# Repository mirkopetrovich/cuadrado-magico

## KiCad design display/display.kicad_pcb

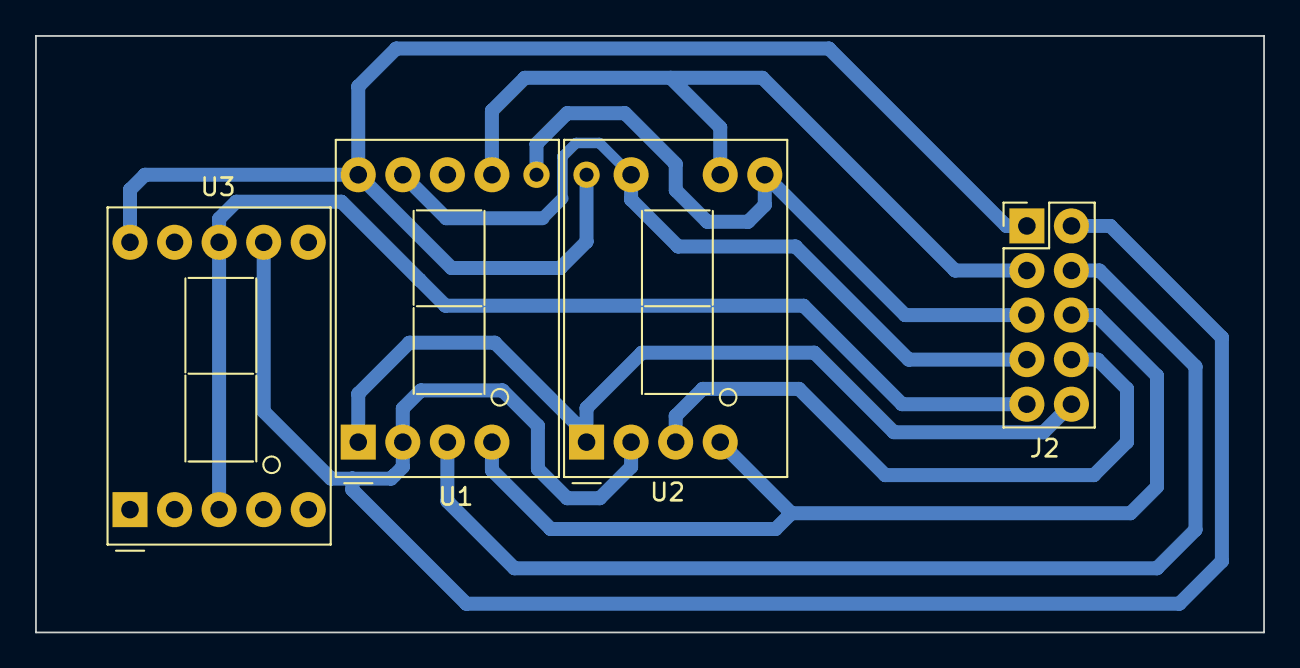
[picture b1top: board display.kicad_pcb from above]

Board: 2 copper layers, 70.0 x 34.0 mm, 4 parts (0 on the bottom side), 10 nets.

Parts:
J2: Conn_02x05_Odd_Even; PinHeader_2x05_P2.54mm_Vertical
U1, U2, U3: D148K; D1X8K

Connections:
/a: J2.3, U1.7 (A), U2.7 (A)
/b: J2.5, U1.6 (B), U2.6 (B)
/c: J2.6, U1.4 (C), U2.4 (C)
/cs1: J2.4, U1.3 (CC), U1.8 (CC)
/cs2: J2.8, U2.3 (CC)
/cs3: J2.9, U3.3 (CC), U3.8 (CC)
/d: J2.2, U1.2 (D), U2.2 (D), U3.7 (A)
/e: J2.10, U1.1 (E), U2.1 (E)
/f: J2.7, U1.9 (F), U2.9 (F)
/g: J2.1, U1.10 (G), U2.10 (G), U3.10 (G)

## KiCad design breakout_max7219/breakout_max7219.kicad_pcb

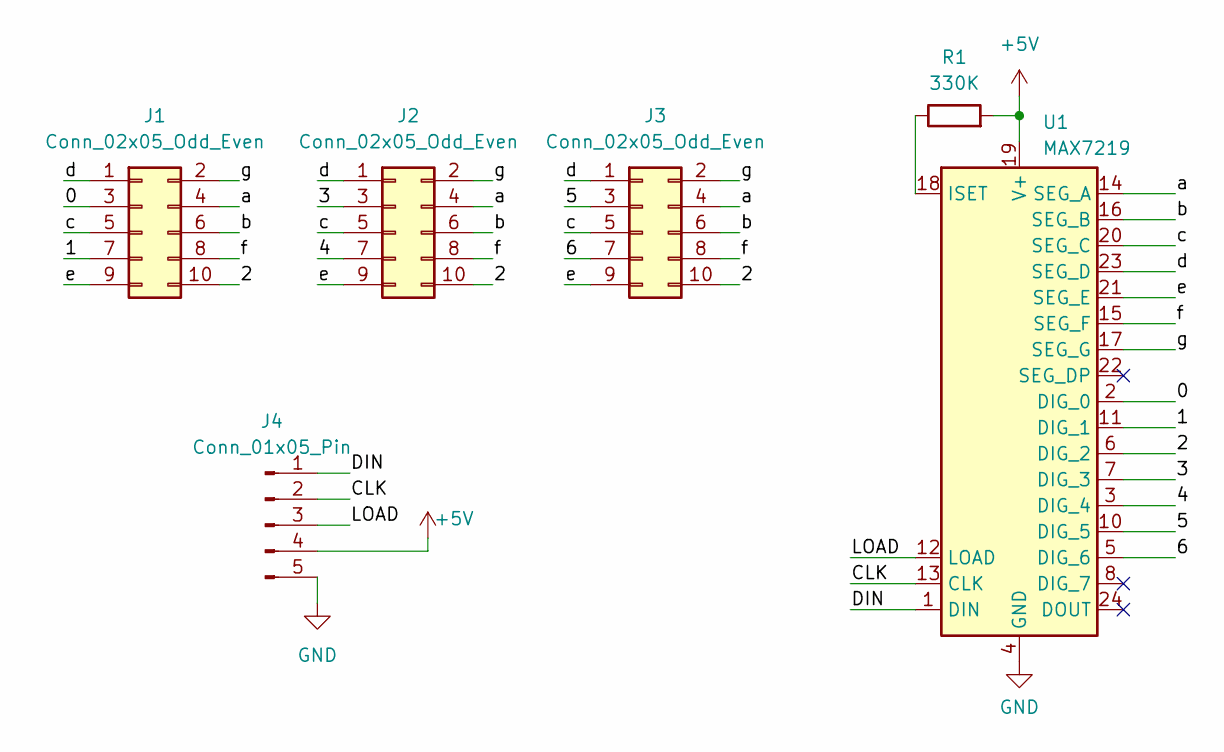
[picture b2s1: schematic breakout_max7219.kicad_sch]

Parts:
J1, J2, J3: Conn_02x05_Odd_Even; PinHeader_2x05_P2.54mm_Vertical
J4: Conn_01x05_Pin; PinHeader_1x05_P2.54mm_Vertical
R1: 330K; R_Axial_DIN0207_L6.3mm_D2.5mm_P10.16mm_Horizontal
U1: MAX7219; DIP-24_W7.62mm_Socket

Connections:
+5V: J4.4, R1.2, U1.19 (V+)
/0: J1.3, U1.2 (DIG_0)
/1: J1.7, U1.11 (DIG_1)
/2: J1.10, J2.10, J3.10, U1.6 (DIG_2)
/3: J2.3, U1.7 (DIG_3)
/4: J2.7, U1.3 (DIG_4)
/5: J3.3, U1.10 (DIG_5)
/6: J3.7, U1.5 (DIG_6)
/CLK: J4.2, U1.13 (CLK)
/DIN: J4.1, U1.1 (DIN)
/LOAD: J4.3, U1.12 (LOAD)
/a: J1.4, J2.4, J3.4, U1.14 (SEG_A)
/b: J1.6, J2.6, J3.6, U1.16 (SEG_B)
/c: J1.5, J2.5, J3.5, U1.20 (SEG_C)
/d: J1.1, J2.1, J3.1, U1.23 (SEG_D)
/e: J1.9, J2.9, J3.9, U1.21 (SEG_E)
/f: J1.8, J2.8, J3.8, U1.15 (SEG_F)
/g: J1.2, J2.2, J3.2, U1.17 (SEG_G)
GND: J4.5, U1.4 (GND), U1.9 (GND)
unnamed: R1.1, U1.18 (ISET)

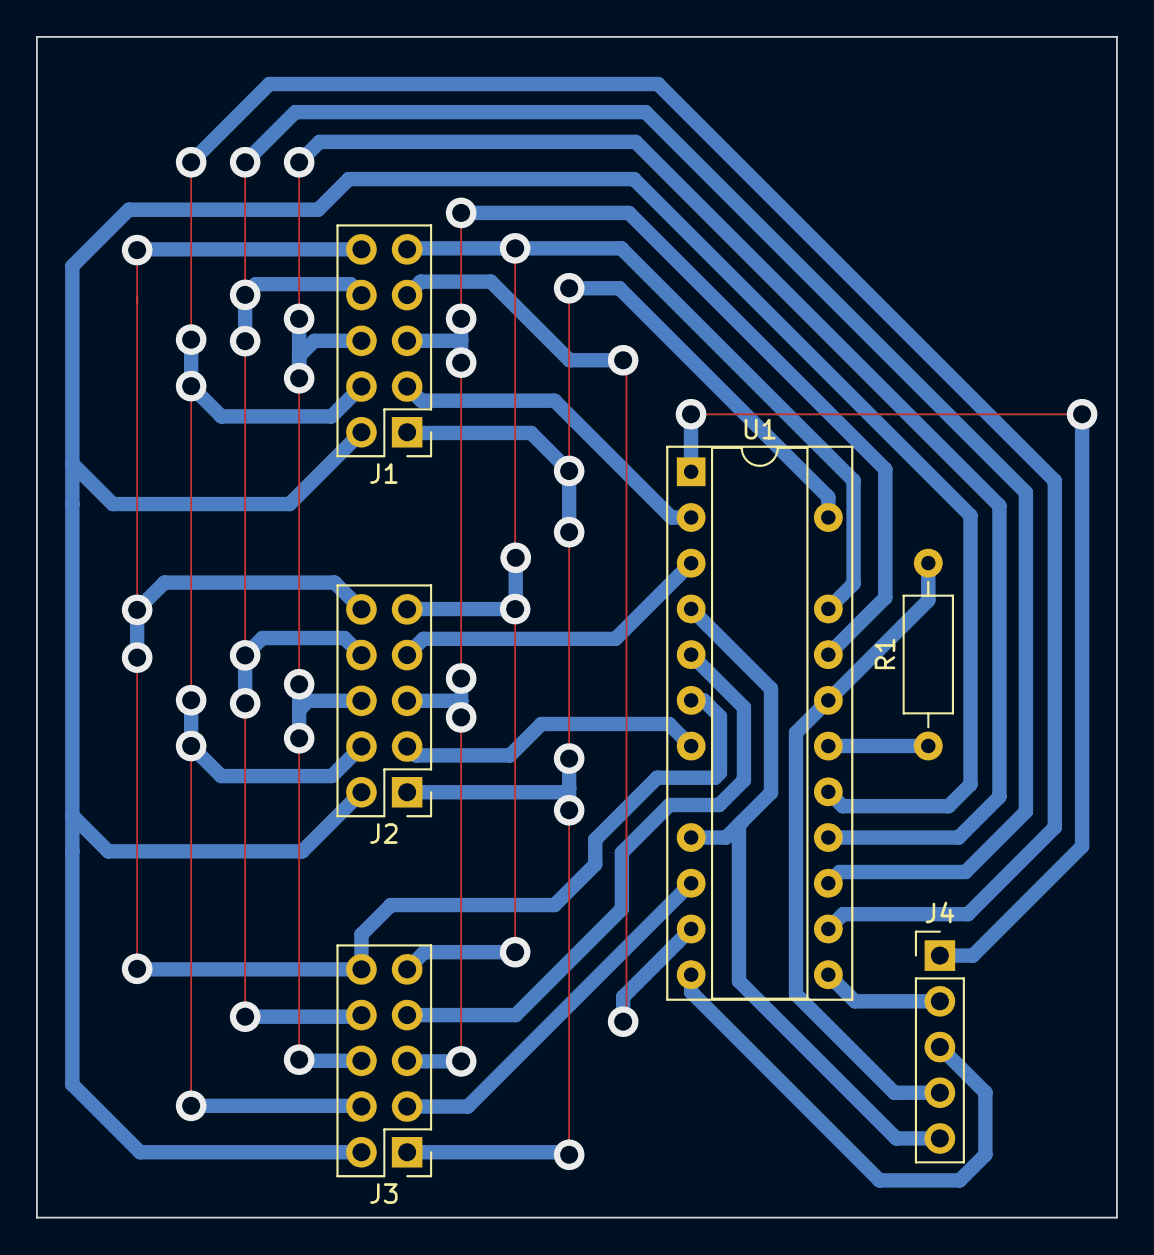
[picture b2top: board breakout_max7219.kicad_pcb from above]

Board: 2 copper layers, 60.0 x 65.6 mm, 6 parts (0 on the bottom side), 20 nets.

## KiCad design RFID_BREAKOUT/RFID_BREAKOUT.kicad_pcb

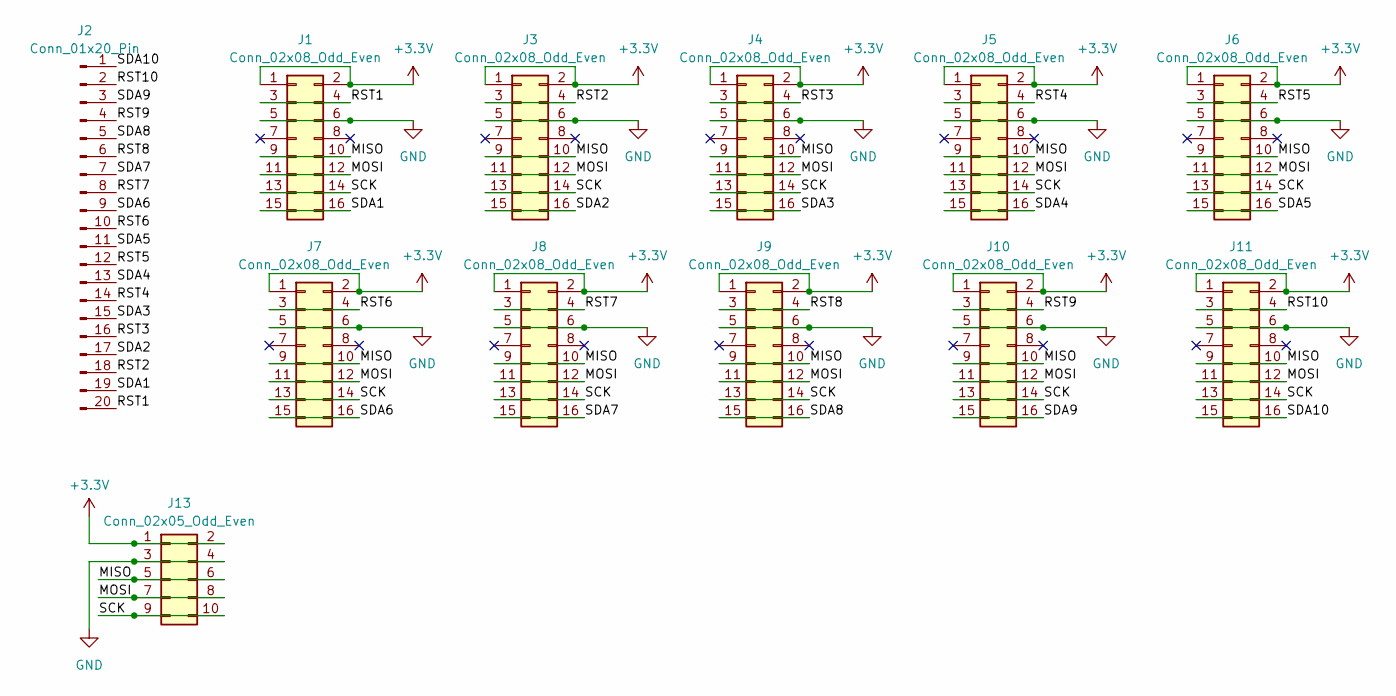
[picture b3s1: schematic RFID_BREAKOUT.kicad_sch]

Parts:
J1, J3, J4, J5, J6, J7, J8, J9, J10, J11: Conn_02x08_Odd_Even; PinHeader_2x08_P2.54mm_Vertical
J2: Conn_01x20_Pin; PinHeader_2x10_P2.54mm_Vertical
J13: Conn_02x05_Odd_Even; PinHeader_2x05_P2.54mm_Vertical

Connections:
+3.3V: J1.1, J1.2, J3.1, J3.2, J4.1, J4.2, J5.1, J5.2, J6.1, J6.2, J7.1, J7.2, J8.1, J8.2, J9.1, J9.2, J10.1, J10.2, J11.1, J11.2, J13.1, J13.2
/MISO: J1.9, J1.10, J3.9, J3.10, J4.9, J4.10, J5.9, J5.10, J6.9, J6.10, J7.9, J7.10, J8.9, J8.10, J9.9, J9.10, J10.9, J10.10, J11.9, J11.10, J13.5, J13.6
/MOSI: J1.11, J1.12, J3.11, J3.12, J4.11, J4.12, J5.11, J5.12, J6.11, J6.12, J7.11, J7.12, J8.11, J8.12, J9.11, J9.12, J10.11, J10.12, J11.11, J11.12, J13.7, J13.8
/RST1: J1.3, J1.4, J2.20
/RST2: J2.18, J3.3, J3.4
/RST3: J2.16, J4.3, J4.4
/RST4: J2.14, J5.3, J5.4
/RST5: J2.12, J6.3, J6.4
/RST6: J2.10, J7.3, J7.4
/RST7: J2.8, J8.3, J8.4
/RST8: J2.6, J9.3, J9.4
/RST9: J2.4, J10.3, J10.4
/RST10: J2.2, J11.3, J11.4
/SCK: J1.13, J1.14, J3.13, J3.14, J4.13, J4.14, J5.13, J5.14, J6.13, J6.14, J7.13, J7.14, J8.13, J8.14, J9.13, J9.14, J10.13, J10.14, J11.13, J11.14, J13.9, J13.10
/SDA1: J1.15, J1.16, J2.19
/SDA2: J2.17, J3.15, J3.16
/SDA3: J2.15, J4.15, J4.16
/SDA4: J2.13, J5.15, J5.16
/SDA5: J2.11, J6.15, J6.16
/SDA6: J2.9, J7.15, J7.16
/SDA7: J2.7, J8.15, J8.16
/SDA8: J2.5, J9.15, J9.16
/SDA9: J2.3, J10.15, J10.16
/SDA10: J2.1, J11.15, J11.16
GND: J1.5, J1.6, J3.5, J3.6, J4.5, J4.6, J5.5, J5.6, J6.5, J6.6, J7.5, J7.6, J8.5, J8.6, J9.5, J9.6, J10.5, J10.6, J11.5, J11.6, J13.3, J13.4

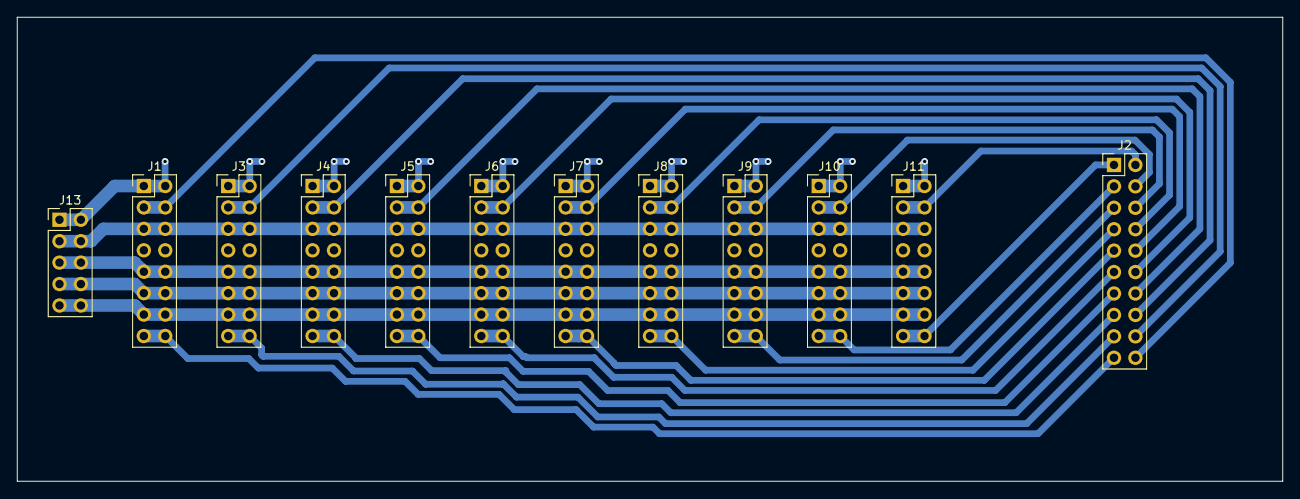
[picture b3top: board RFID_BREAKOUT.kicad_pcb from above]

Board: 2 copper layers, 150.0 x 55.0 mm, 12 parts (0 on the bottom side), 25 nets.

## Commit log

2024-09-04 colores
2024-10-14 materiales
2024-10-14 RFID BREAKOUT
2024-10-15 display mod + plano
2024-10-15 15oct
2024-10-16 update display pcb
2024-10-24 mod display
2024-11-11 nuevo display
2025-05-23 3 sketch arduino
2025-05-24 delay MAESTRO + opcion TFT
2025-06-04 test esclavos
2025-06-04 probador
2025-06-05 probadorX3
2025-06-25 test matrix
2025-06-25 random color
